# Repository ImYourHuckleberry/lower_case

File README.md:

# lower_case

# uhoh
# You've probably gotten here by mistake
See this is a 32 key buckling spring keyboard inspired by the IBM Model F.
In order to have actually wanted to arrive on this page you need to be:
1) Interested in mechanichal keyboards
2) Interested in vintage keyboards
3) Interested in tiny keyboards
4) Absurdly tiny keyboards
5) Willing to order a spec pcb by someone with no education or right making such a thing
6) Able to get your hands on the necessarry flippers, springs, controllers, barrels, and drivers needed to actually make any of this work
7) Pretty cool

# WARNING

You better use a solenoid in this, if you don't I'll know and I'll find you and take your board away and start discord trash talk. If I ever find out someone tries to make this linear I am taking my proverbial ball offline and going home.

# Renders

# Actual Picture

#some notes
PCB, 3MF, and STEP files for the lower case capacative keyboard

right now I dont even know if this will work!

If you are just looking to make the pcb you need these. The ground plate is necessarry, dont skip it. I went with 0.8 for thickness

lowercase/gerber_pcb.zip
lowercase/gnd_gerber.zip

3D parts should be in there. I have printed them and they look good and fit well. I am using threaded insert embedded nuts to screw on the mounting bracket. 
Basically a little threaded pipe you heat up with a soldering iron and it embeds into the print. This way you have something to actually screw into.

The plate could use some spacebar stab mounts, Im looking into it

Basically you need the case cause of course you do. The plate is curved so IDK how else you could get one. The mounting bracket snugs the whole thing up.

# How do all the components fit
# Good question!!

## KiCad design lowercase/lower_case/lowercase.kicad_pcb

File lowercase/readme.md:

# LOWERCASE

#I haven't even recieved my plates yet so good luck and god speed

QAZ layout based IBM Model F

(https://github.com/purdeaandrei/SMDModelFController).
(https://github.com/purdeaandrei/SolenoidDriver).

if you order through JLCPCB you can have them assemble it you you using files found in the repo

The ground plate is important to avoid interference and is to be placed beneath the main pcb. I recommend soldering connections on the front of the main pcb and back of the ground plate to allow a flush fit.

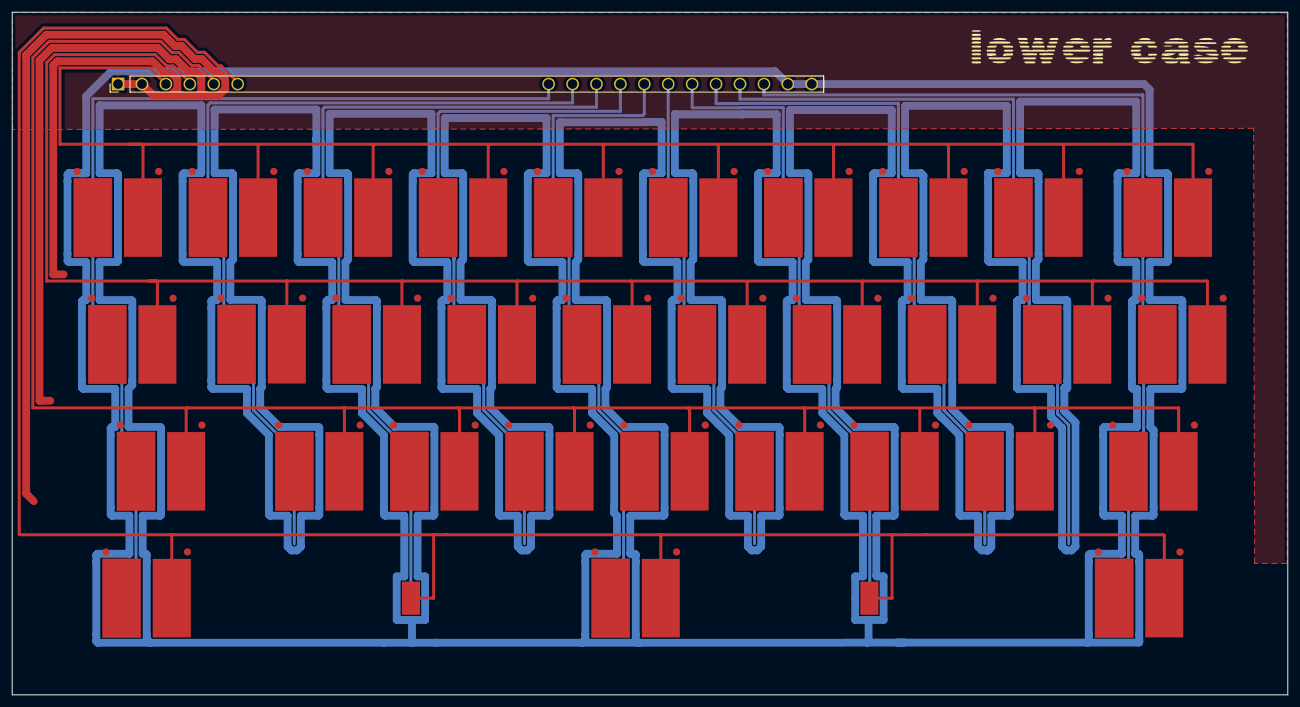
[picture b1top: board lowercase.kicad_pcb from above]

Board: 2 copper layers, 211.2 x 113.0 mm, 35 parts (0 on the bottom side), 15 nets.

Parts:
J1: Conn_01x30; Model_F_3.96mm_pitch_footprint
SW1, SW3, SW4, SW5, SW7, SW8, SW9, SW11, SW12, SW13, SW15, SW17, SW19, SW21, SW23, SW25, SW26, SW27, SW29, SW31, SW33, SW35, SW37: SW_Cap; capswitch2
SW50, SW51: SW_Cap; testpad
locked: SW_Cap; capswitch2
locked#2, locked#3, locked#4, locked#5, locked#6, locked#7, locked#8, locked#9: SW_Cap; capswitch2

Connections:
C0: J1.19, SW1.DRIVE, SW3.DRIVE, SW4.DRIVE, locked.DRIVE
C1: J1.20, SW5.DRIVE, SW7.DRIVE, locked#2.DRIVE
C2: J1.21, SW9.DRIVE, SW11.DRIVE, SW50.DRIVE, locked#3.DRIVE
C3: J1.22, SW13.DRIVE, SW15.DRIVE, locked#4.DRIVE
C4: J1.23, SW8.DRIVE, SW17.DRIVE, SW19.DRIVE, locked#5.DRIVE
C5: J1.24, SW21.DRIVE, SW23.DRIVE, locked#6.DRIVE
C6: J1.25, SW25.DRIVE, SW26.DRIVE, SW27.DRIVE, SW51.DRIVE
C7: J1.26, SW29.DRIVE, SW31.DRIVE, locked#7.DRIVE
C8: J1.27, SW33.DRIVE, locked#8.DRIVE
C9: J1.28, SW12.DRIVE, SW35.DRIVE, SW37.DRIVE, locked#9.DRIVE
GND: J1.1, J1.2, J1.29, J1.30, SW1.GND, SW3.GND, SW4.GND, SW5.GND, SW7.GND, SW8.GND, SW9.GND, SW11.GND, SW12.GND, SW13.GND, SW15.GND, SW17.GND, SW19.GND, SW21.GND, SW23.GND, SW25.GND, SW26.GND, SW27.GND, SW29.GND, SW31.GND, SW33.GND, SW35.GND, SW37.GND, SW50.GND, SW51.GND, locked.GND, locked#2.GND, locked#3.GND, locked#4.GND, locked#5.GND, locked#6.GND, locked#7.GND, locked#8.GND, locked#9.GND
R0: J1.3, SW1.SENSE, SW5.SENSE, SW9.SENSE, SW13.SENSE, SW17.SENSE, SW21.SENSE, SW25.SENSE, SW29.SENSE, SW33.SENSE, SW37.SENSE
R1: J1.4, SW26.SENSE, locked.SENSE, locked#2.SENSE, locked#3.SENSE, locked#4.SENSE, locked#5.SENSE, locked#6.SENSE, locked#7.SENSE, locked#8.SENSE, locked#9.SENSE
R2: J1.5, SW3.SENSE, SW7.SENSE, SW11.SENSE, SW15.SENSE, SW19.SENSE, SW23.SENSE, SW27.SENSE, SW31.SENSE, SW35.SENSE
R3: J1.6, SW4.SENSE, SW8.SENSE, SW12.SENSE, SW50.SENSE, SW51.SENSE
